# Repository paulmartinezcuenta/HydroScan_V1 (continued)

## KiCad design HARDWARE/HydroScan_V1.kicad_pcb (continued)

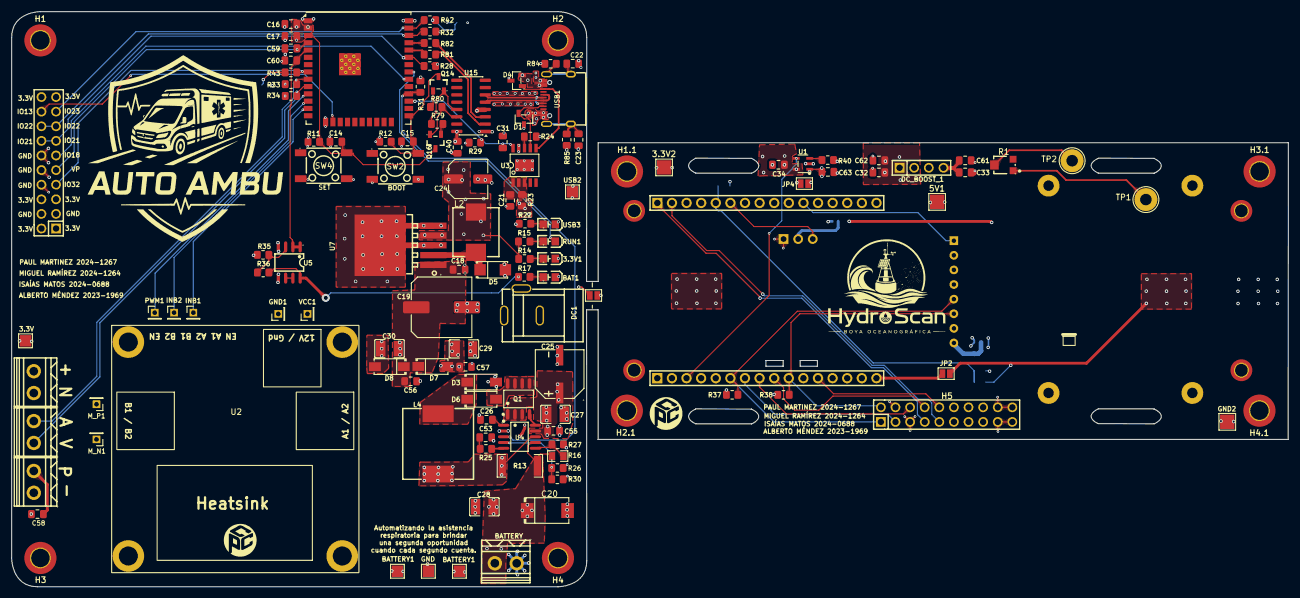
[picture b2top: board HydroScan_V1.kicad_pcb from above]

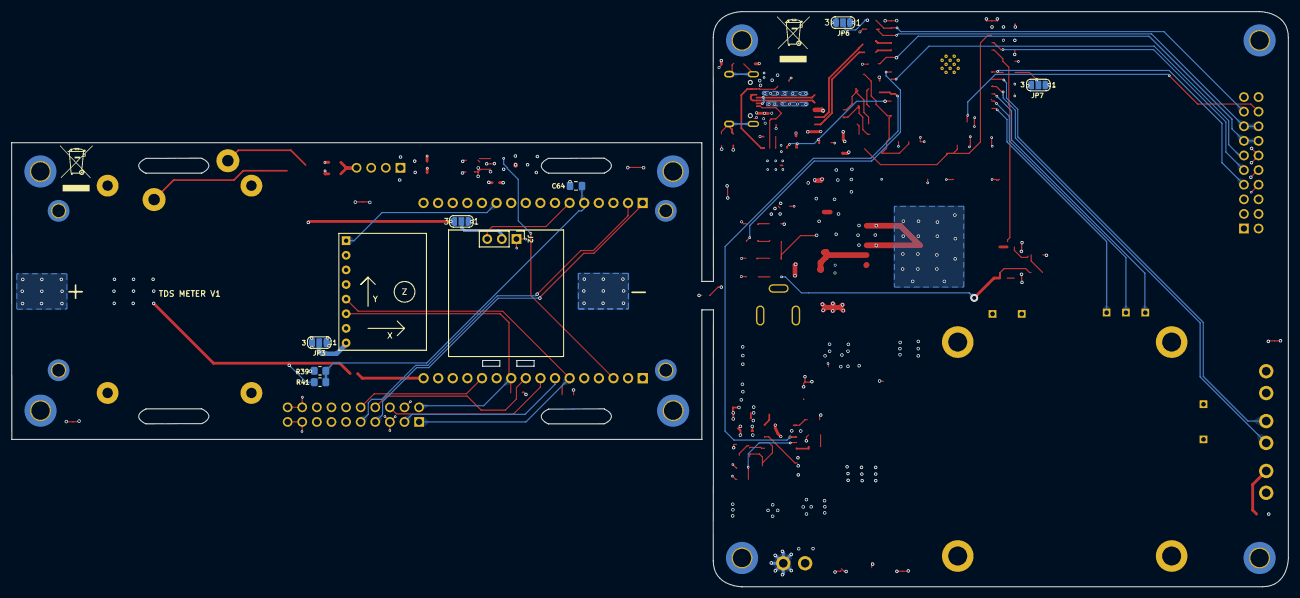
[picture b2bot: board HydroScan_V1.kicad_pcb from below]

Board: 4 copper layers, 222.0 x 100.0 mm, 153 parts (9 on the bottom side), 82 nets.

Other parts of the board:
1A: LOGO; 13
H1, H1.1, H2#2, H2.1, H3, H3.1, H4, H4.1: MountingHole_3.2mm_M3_DIN965_Pad_TopBottom
H7.1, H7.2, H7.3, H7.4: (no value)
H8.1, H8.2, H8.3, H8.4: MountingHole_2.2mm_M2_DIN965_Pad_TopBottom
THECPCENTER: LOGO; IMG1
THECPCENTER#2: LOGO; IMG1
U2: L298N; L298N-module-43x43mm
_: modulo esp32

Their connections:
GND: H7.1.1, H7.2.1, H7.3.1, H7.4.1, H8.1.1, H8.2.1, H8.3.1; also elsewhere on the board

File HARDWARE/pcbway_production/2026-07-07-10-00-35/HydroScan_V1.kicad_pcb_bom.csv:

Designator,Quantity,Value,Footprint,Package,MPN,DNP,Mount_Type,LCSC Part,Description,KiLib_Generator,LCSC,Manufacturer
"3.3V1, BAT1, RUN1, USB3",4,YLED0805G,LED0805-FD-GREEN,,,,smt,C25170728,,,,
"C14, C15, C22, C23, C26, C55, C56, C57, C58, C59, C60",11,0.1uf,C_0805_2012Metric_Pad1.18x1.45mm_HandSolder,,,,smt,,Unpolarized capacitor,SMD_2terminal_chip_molded,,
"C16, C18, C31, C40",4,100nf,C_0805_2012Metric_Pad1.18x1.45mm_HandSolder,,,,smt,,Unpolarized capacitor,SMD_2terminal_chip_molded,,
C17,1,10uf_25v,C_0805_2012Metric_Pad1.18x1.45mm_HandSolder,,,,smt,,Unpolarized capacitor,SMD_2terminal_chip_molded,,
C19,1,470uf,C_Elec_10x10.2,,,,smt,,Polarized capacitor,capacitor/SMD/elec_round,C72518,
C20,1,CA45-D035K226T,CAP-SMD_L7.3-W4.3-R-RD,,CA45-D035K226T,,smt,C126947,,,,湘怡中元/湘江
C21,1,1uf,C_0805_2012Metric_Pad1.18x1.45mm_HandSolder,,,,smt,,Unpolarized capacitor,SMD_2terminal_chip_molded,,
C24,1,47uf,C_Elec_6.3x7.7,,,,smt,,Polarized capacitor,capacitor/SMD/elec_round,C72523,
C25,1,RVT1V221M0810,CAP-SMD_BD8.0-L8.3-W8.3-LS9.1-FD,,RVT1V221M0810,,smt,C3340,220uF 35V,,,HONOR(荣誉)
"C27, C28, C29, C30",4,CL32B106KBJNNNE,C1210,,CL32B106KBJNNNE,,smt,C138687,,,,SAMSUNG(三星)
C53,1,220nF,C_0805_2012Metric_Pad1.18x1.45mm_HandSolder,,,,smt,,Unpolarized capacitor,SMD_2terminal_chip_molded,,
"D1, D4",2,SM05.TCT,SOT-23-3_L2.9-W1.3-P0.95-LS2.4-BR,,SM05.TCT,,smt,C85197,,,,SEMTECH
"D3, D6, D7, D8",4,SS54_C22452,SMA_L4.4-W2.8-LS5.4-R-RD,,SS54,,smt,C22452,SS54,,,MDD(辰达半导体)
D5,1,B330A,SMA_L4.3-W2.6-LS5.1-RD,,B330A,,tht,C52037930,,,,GOODWORK(固得沃克)
GND1,1,PH_GND,PinHeader_1x01_P2.00mm_Vertical,,,,tht,,test point,connector/pin_header_socket,,
H2,1,2.54-2*10,HDR-TH_20P-P2.54-V-M-R2-C10-S2.54,,2.54-2*10,,tht,C5116480,,,,ZHOURI(洲日)
INB1,1,INB1,PinHeader_1x01_P2.00mm_Vertical,,,,tht,,test point,connector/pin_header_socket,,
INB2,1,INB2,PinHeader_1x01_P2.00mm_Vertical,,,,tht,,test point,connector/pin_header_socket,,
L2,1,PSPMAA0805-101M-ANP,IND-SMD_L8.5-W8.0_PCC-M0854M,,,,smt,C2962892,,,,
L4,1,SMDRI127-220MT,IND-SMD_L12.3-W12.3_SMDRI127,,SMDRI127-220MT,,smt,C9905,,,,SXN(顺翔诺)
M_N1,1,M_N,PinHeader_1x01_P2.00mm_Vertical,,,,tht,,test point,connector/pin_header_socket,,
M_P1,1,TestPoint,PinHeader_1x01_P2.00mm_Vertical,,,,tht,,test point,connector/pin_header_socket,,
PWM1,1,PWM,PinHeader_1x01_P2.00mm_Vertical,,,,tht,,test point,connector/pin_header_socket,,
Q1,1,AO4435_C2944310,SOP-8_L5.0-W3.8-P1.27-LS6.0-BL,,AO4435,,smt,C2944310,,,,UMW(友台半导体)
"Q14, Q16",2,2n3904S-RTK/PS_C18536,SOT-23-3_L2.9-W1.3-P1.90-LS2.4-TR,,,,smt,C18536,,,,
"R11, R12, R24, R26, R29, R31, R35",7,10k,R_0805_2012Metric_Pad1.20x1.40mm_HandSolder,,,,smt,,Resistor,SMD_2terminal_chip_molded,,
R13,1,YLRY12-3-60F,R2512,,YLRY12-3-60F,,tht,C22468068,,,,yezhan(业展)
"R14, R15, R17, R22",4,2.2k,R_0805_2012Metric_Pad1.20x1.40mm_HandSolder,,,,smt,,Resistor,SMD_2terminal_chip_molded,,
R16,1,RC0805FR-07390KL,R0805,,RC0805FR-07390KL,,smt,C137535,,,,YAGEO(国巨)
"R23, R79, R80",3,1k,R_0805_2012Metric_Pad1.20x1.40mm_HandSolder,,,,smt,,Resistor,SMD_2terminal_chip_molded,,
R25,1,120,R_0805_2012Metric_Pad1.20x1.40mm_HandSolder,,,,smt,,Resistor,SMD_2terminal_chip_molded,,
R27,1,41.2K,R_0805_2012Metric_Pad1.20x1.40mm_HandSolder,,,,smt,,Resistor,SMD_2terminal_chip_molded,C2077335,
"R28, R32, R33, R34",4,4.7K,R_0805_2012Metric_Pad1.20x1.40mm_HandSolder,,,,smt,,Resistor,SMD_2terminal_chip_molded,,
R30,1,100K,R_0805_2012Metric_Pad1.20x1.40mm_HandSolder,,,,smt,,Resistor,SMD_2terminal_chip_molded,,
R36,1,30k,R_0805_2012Metric_Pad1.20x1.40mm_HandSolder,,,,smt,,Resistor,SMD_2terminal_chip_molded,,
"R81, R82",2,0,R_0805_2012Metric_Pad1.20x1.40mm_HandSolder,,,,smt,,Resistor,SMD_2terminal_chip_molded,,
"R84, R85",2,1M,R_0805_2012Metric_Pad1.20x1.40mm_HandSolder,,,,smt,,Resistor,SMD_2terminal_chip_molded,,
SW2,1,BOOT,SW-SMD_4P-L6.0-W6.0-P4.50-LS8.2,,,,tht,C7528752,,,,
SW4,1,RESET,SW-SMD_4P-L6.0-W6.0-P4.50-LS8.2,,,,tht,C7528752,,,,
"U10, U11, U8, U9",4,DB125-3.81-2P-BK-S,CONN-TH_2P-P3.81_DB125-3.81-2P-BK-S,,DB125-3.81-2P-BK-S,,tht,C430618,,,,DORABO(地博电气)
U15,1,CH340C,SOIC-16_3.9x9.9mm_P1.27mm,,,,smt,,"USB serial converter, crystal-less, UART, SOIC-16",package/gullwing,,
U16,1,ESP32-WROOM-32D,ESP32-WROOM-32U,,,,smt,,"RF Module, ESP32-D0WD SoC, Wi-Fi 802.11b/g/n, Bluetooth, BLE, 32-bit, 2.7-3.6V, onboard antenna, SMD",,,
U2,1,L298N,L298N-module-43x43mm,,,,tht,,test point,,,
U3,1,CH224K,ESSOP-10_L4.9-W3.9-P1.0-LS6.0-TL-EP,,CH224K,,smt,C970725,,,,WCH(南京沁恒)
U4,1,CN3795,SSOP-10_L4.9-W3.9-P1.00-LS6.0-BL,,CN3795,,smt,C150555,,,,CONSONANCE(上海如韵)
U5,1,LM358DR,SOIC-8_L5.0-W4.0-P1.27-LS6.0-BL,,LM358DR,,smt,C5423,,,,TI(德州仪器)
U7,1,LM2576HVS-3.3,PG-TO-263-5_L10.2-W8.7-P1.70-LS14.4-BR,,,,smt,C347436,,,,
USB1,1,TYPE-C 16PIN 2MD,USB-C-SMD_TYPE-C-16PIN-2MD-073,,TYPE-C 16PIN 2MD(073),,smt,C2765186,,,,SHOU HAN(首韩)
VCC1,1,M_VCC,PinHeader_1x01_P2.00mm_Vertical,,,,tht,,test point,connector/pin_header_socket,,

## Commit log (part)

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2026-06-11 primer commit HydroScan V1
2026-06-11 agregar gitignore y excluir historial
2026-06-11 Organizacion de trabajo
2026-06-11 Add project overview to README
2026-06-11 Organización
2026-06-11 Update README with HydroScan V1 project details
    Added detailed project description and features for HydroScan V1.
2026-06-14 PCB dimensions
2026-06-14 Edit of schematic
2026-06-15 Integrate ESP32
2026-06-16 Aclaracion de avances
2026-06-18 Avances puerto USB C
2026-06-18 Avances v1
2026-06-18 change 2
2026-06-19 EsP32 terminate
2026-06-19 cambios en el fast charging
2026-06-20 USB c and Fast chargin update finish
2026-06-21 update of charging and logic
2026-06-22 power updating
2026-06-23 powering rooting finish
2026-06-24 Update of design the power
    update of charging
2026-06-25 latest updates
